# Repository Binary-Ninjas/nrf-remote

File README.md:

# nrf-remote
ATMEGA328 based remote with joysticks and buttons which uses nRF24L01 radio module

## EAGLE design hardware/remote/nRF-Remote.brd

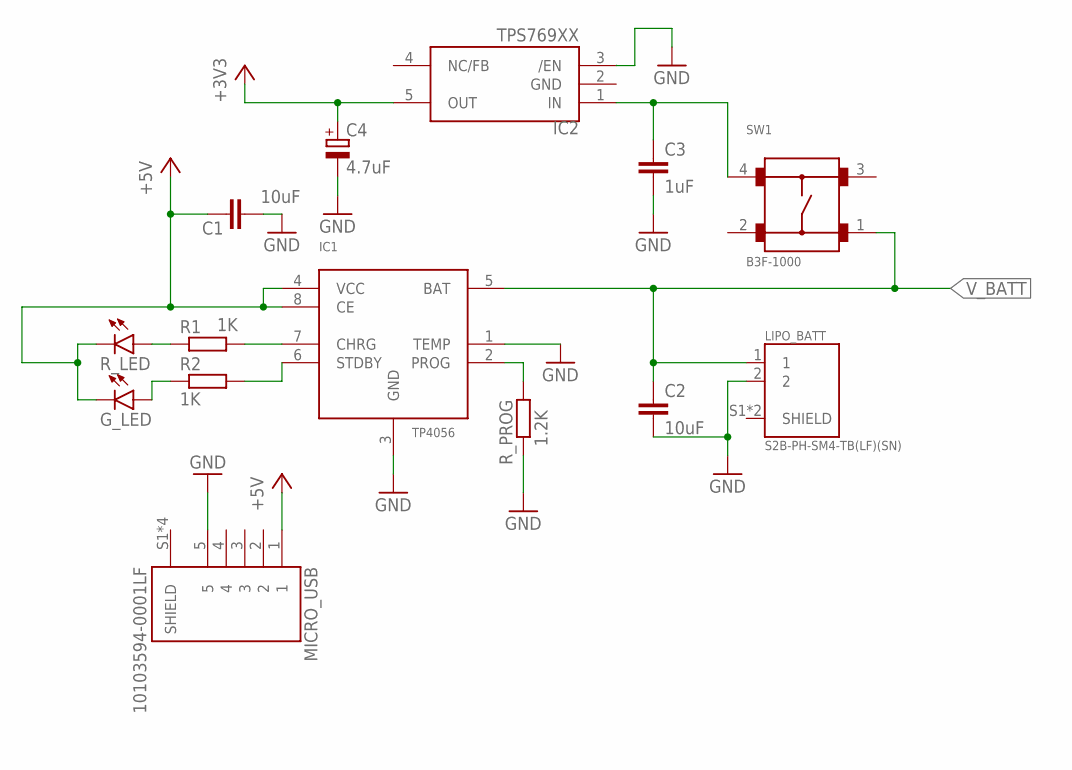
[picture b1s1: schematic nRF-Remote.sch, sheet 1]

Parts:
C1, C2: 10uF; C0603
C3: 1uF; C0603
C4: 4.7uF; 153CLV-0605
G_LED: LEDCHIP-LED0805; CHIP-LED0805
IC1: TP4056; SOP-8
IC2: TPS769XX; SOT23-5L
LIPO_BATT: S2B-PH-SM4-TB(LF)(SN)
MICRO_USB: 10103594-0001LF
R1, R2: 1K; R0603
R_LED: LEDCHIP-LED0805; CHIP-LED0805
R_PROG: 1.2K; R0603
SW1: B3F-1000

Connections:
+3V3: C4.+, IC2.5 (OUT); also elsewhere on the board
+5V: C1.1, G_LED.C, IC1.4 (VCC), IC1.8 (CE), MICRO_USB.1, R_LED.C
GND: C1.2, C2.2, C3.2, C4.-, IC1.1 (TEMP), IC1.3 (GND), IC2.2 (GND), IC2.3 (/EN), LIPO_BATT.2, MICRO_USB.5, R_PROG.1; also elsewhere on the board
unnamed: IC1.7 (CHRG), R1.2
unnamed: IC1.6 (STDBY), R2.2
unnamed: R1.1, R_LED.A
unnamed: G_LED.A, R2.1
unnamed: IC1.2 (PROG), R_PROG.2
unnamed: C3.1, IC2.1 (IN), SW1.4
V_BATT: C2.1, IC1.5 (BAT), LIPO_BATT.1, SW1.1; also elsewhere on the board

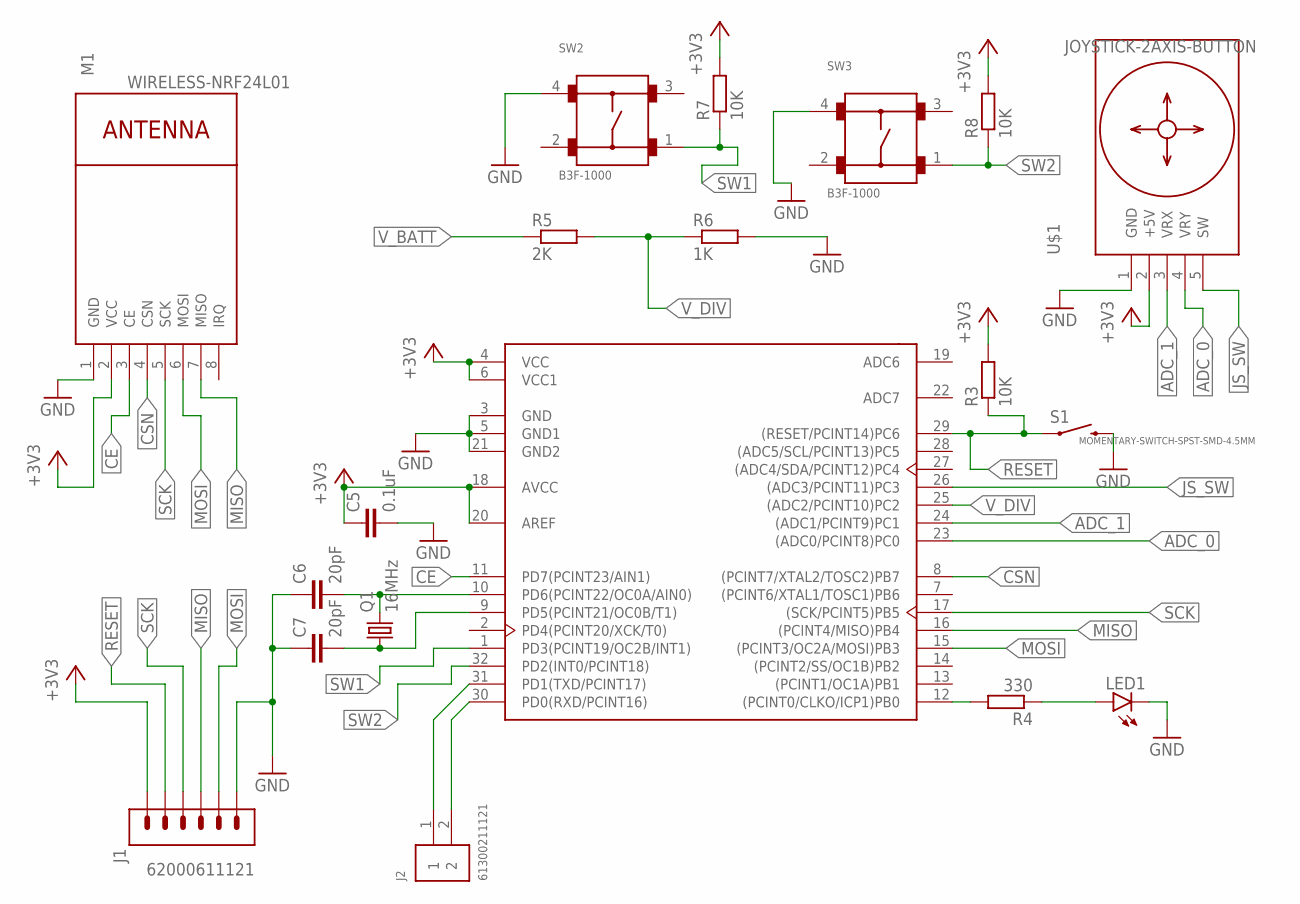
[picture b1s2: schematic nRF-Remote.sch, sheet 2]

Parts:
C5: 0.1uF; C0805
C6, C7: 20pF; C0603
J1: 62000611121
J2: 61300211121
LED1: LEDCHIP-LED0805; CHIP-LED0805
M1: WIRELESS-NRF24L01
Q1: 16MHz; SM49
R3: 10K; R0805
R4: 330; R0805
R5: 2K; R0805
R6: 1K; R0805
R7, R8: 10K; R0603
S1: MOMENTARY-SWITCH-SPST-SMD-4.5MM; TACTILE_SWITCH_SMD_4.5MM
SW2, SW3: B3F-1000
U1: ATMEGA328P-AU; TQFP-32
U$1: JOYSTICK-2AXIS-BUTTON

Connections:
+3V3: C5.1, J1.1, M1.2 (VCC), R3.2, R7.2, R8.2, U1.4 (VCC), U1.6 (VCC1), U1.18 (AVCC), U1.20 (AREF), U$1.2 (+5V); also elsewhere on the board
ADC_0: U1.23 ((ADC0/PCINT8)PC0), U$1.4 (VRY)
ADC_1: U1.24 ((ADC1/PCINT9)PC1), U$1.3 (VRX)
CE: M1.3 (CE), U1.11 (PD7(PCINT23/AIN1))
CSN: M1.4 (CSN), U1.8 ((PCINT7/XTAL2/TOSC2)PB7)
GND: C5.2, C6.1, C7.1, J1.6, LED1.C, M1.1 (GND), R6.2, S1.1 (2), S1.4 (2), SW2.4, SW3.4, U1.3 (GND), U1.5 (GND1), U1.21 (GND2), U$1.1 (GND); also elsewhere on the board
JS_SW: U1.26 ((ADC3/PCINT11)PC3), U$1.5 (SW)
MISO: J1.4, M1.7 (MISO), U1.16 ((PCINT4/MISO)PB4)
MOSI: J1.5, M1.6 (MOSI), U1.15 ((PCINT3/OC2A/MOSI)PB3)
unnamed: R4.2, U1.12 ((PCINT0/CLKO/ICP1)PB0)
unnamed: C6.2, Q1.2, U1.10 (PD6(PCINT22/OC0A/AIN0))
unnamed: LED1.A, R4.1
unnamed: C7.2, Q1.1, U1.9 (PD5(PCINT21/OC0B/T1))
unnamed: J2.2, U1.30 (PD0(RXD/PCINT16))
unnamed: J2.1, U1.31 (PD1(TXD/PCINT17))
RESET: J1.2, R3.1, S1.2 (1), S1.3 (1), U1.29 ((RESET/PCINT14)PC6)
SCK: J1.3, M1.5 (SCK), U1.17 ((SCK/PCINT5)PB5)
SW1: R7.1, SW2.1, U1.1 (PD3(PCINT19/OC2B/INT1))
SW2: R8.1, SW3.1, U1.32 (PD2(INT0/PCINT18))
V_BATT: R5.1; also elsewhere on the board
V_DIV: R5.2, R6.1, U1.25 ((ADC2/PCINT10)PC2)

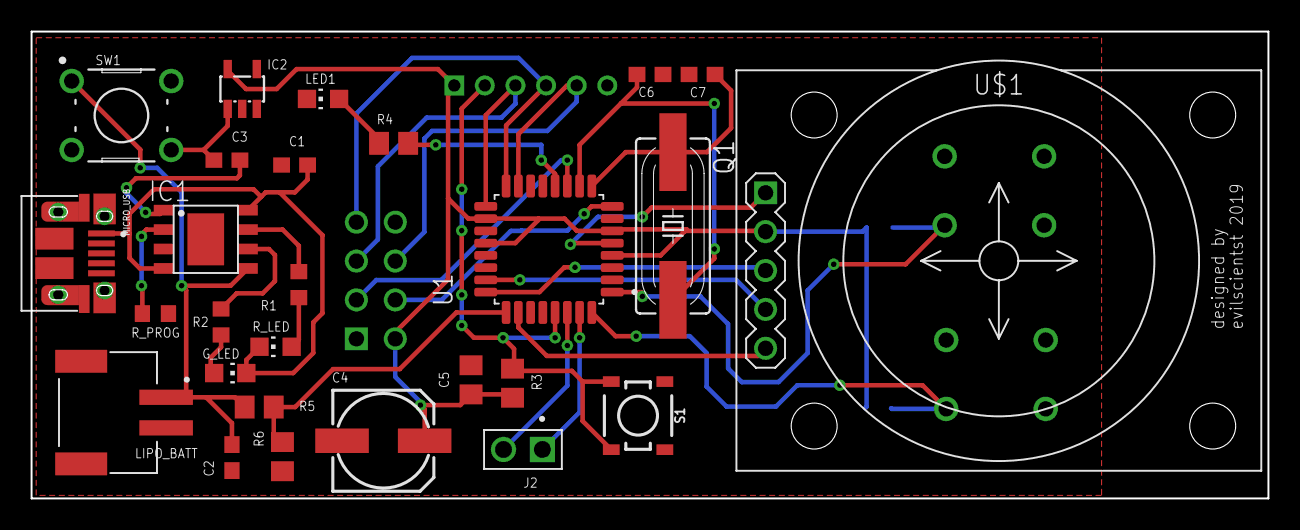
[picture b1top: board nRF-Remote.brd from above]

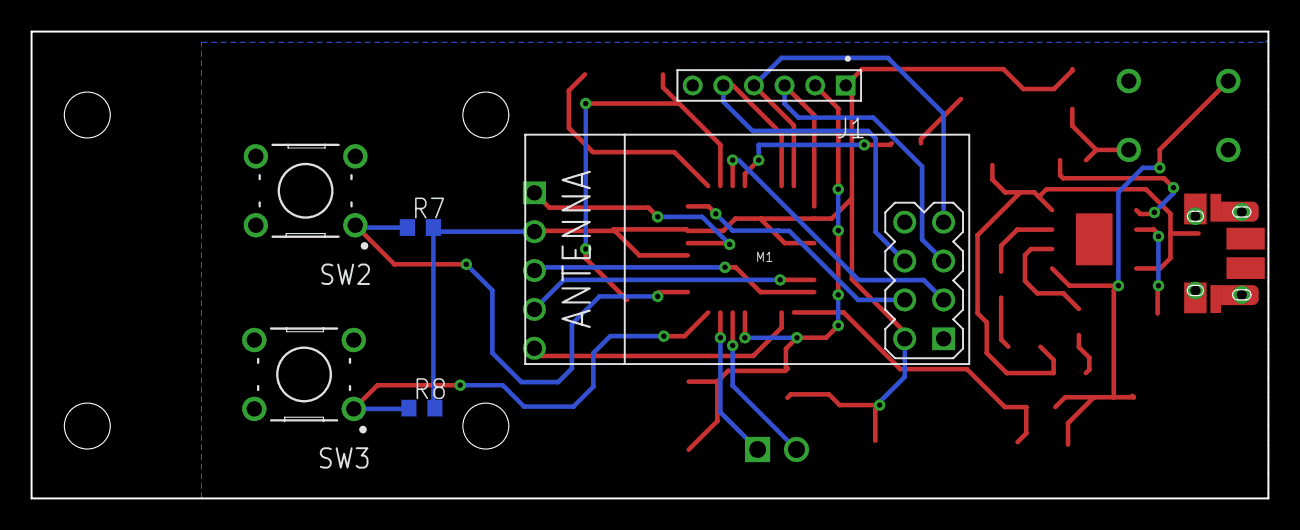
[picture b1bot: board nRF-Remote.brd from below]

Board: 2 copper layers, 80.8 x 30.5 mm, 33 parts (6 on the bottom side), 28 nets.

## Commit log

2019-10-05 Add remote hardware files
2019-10-08 Update design with external XTAL, add buttons

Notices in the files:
parts and their libraries:
diy-modules: Released under the Creative Commons Attribution 4.0 International License: http://creativecommons.org/licenses/by/4.0
SparkFun-Switches: Licensing: Creative Commons ShareAlike 4.0 International - https://creativecommons.org/licenses/by-sa/4.0
